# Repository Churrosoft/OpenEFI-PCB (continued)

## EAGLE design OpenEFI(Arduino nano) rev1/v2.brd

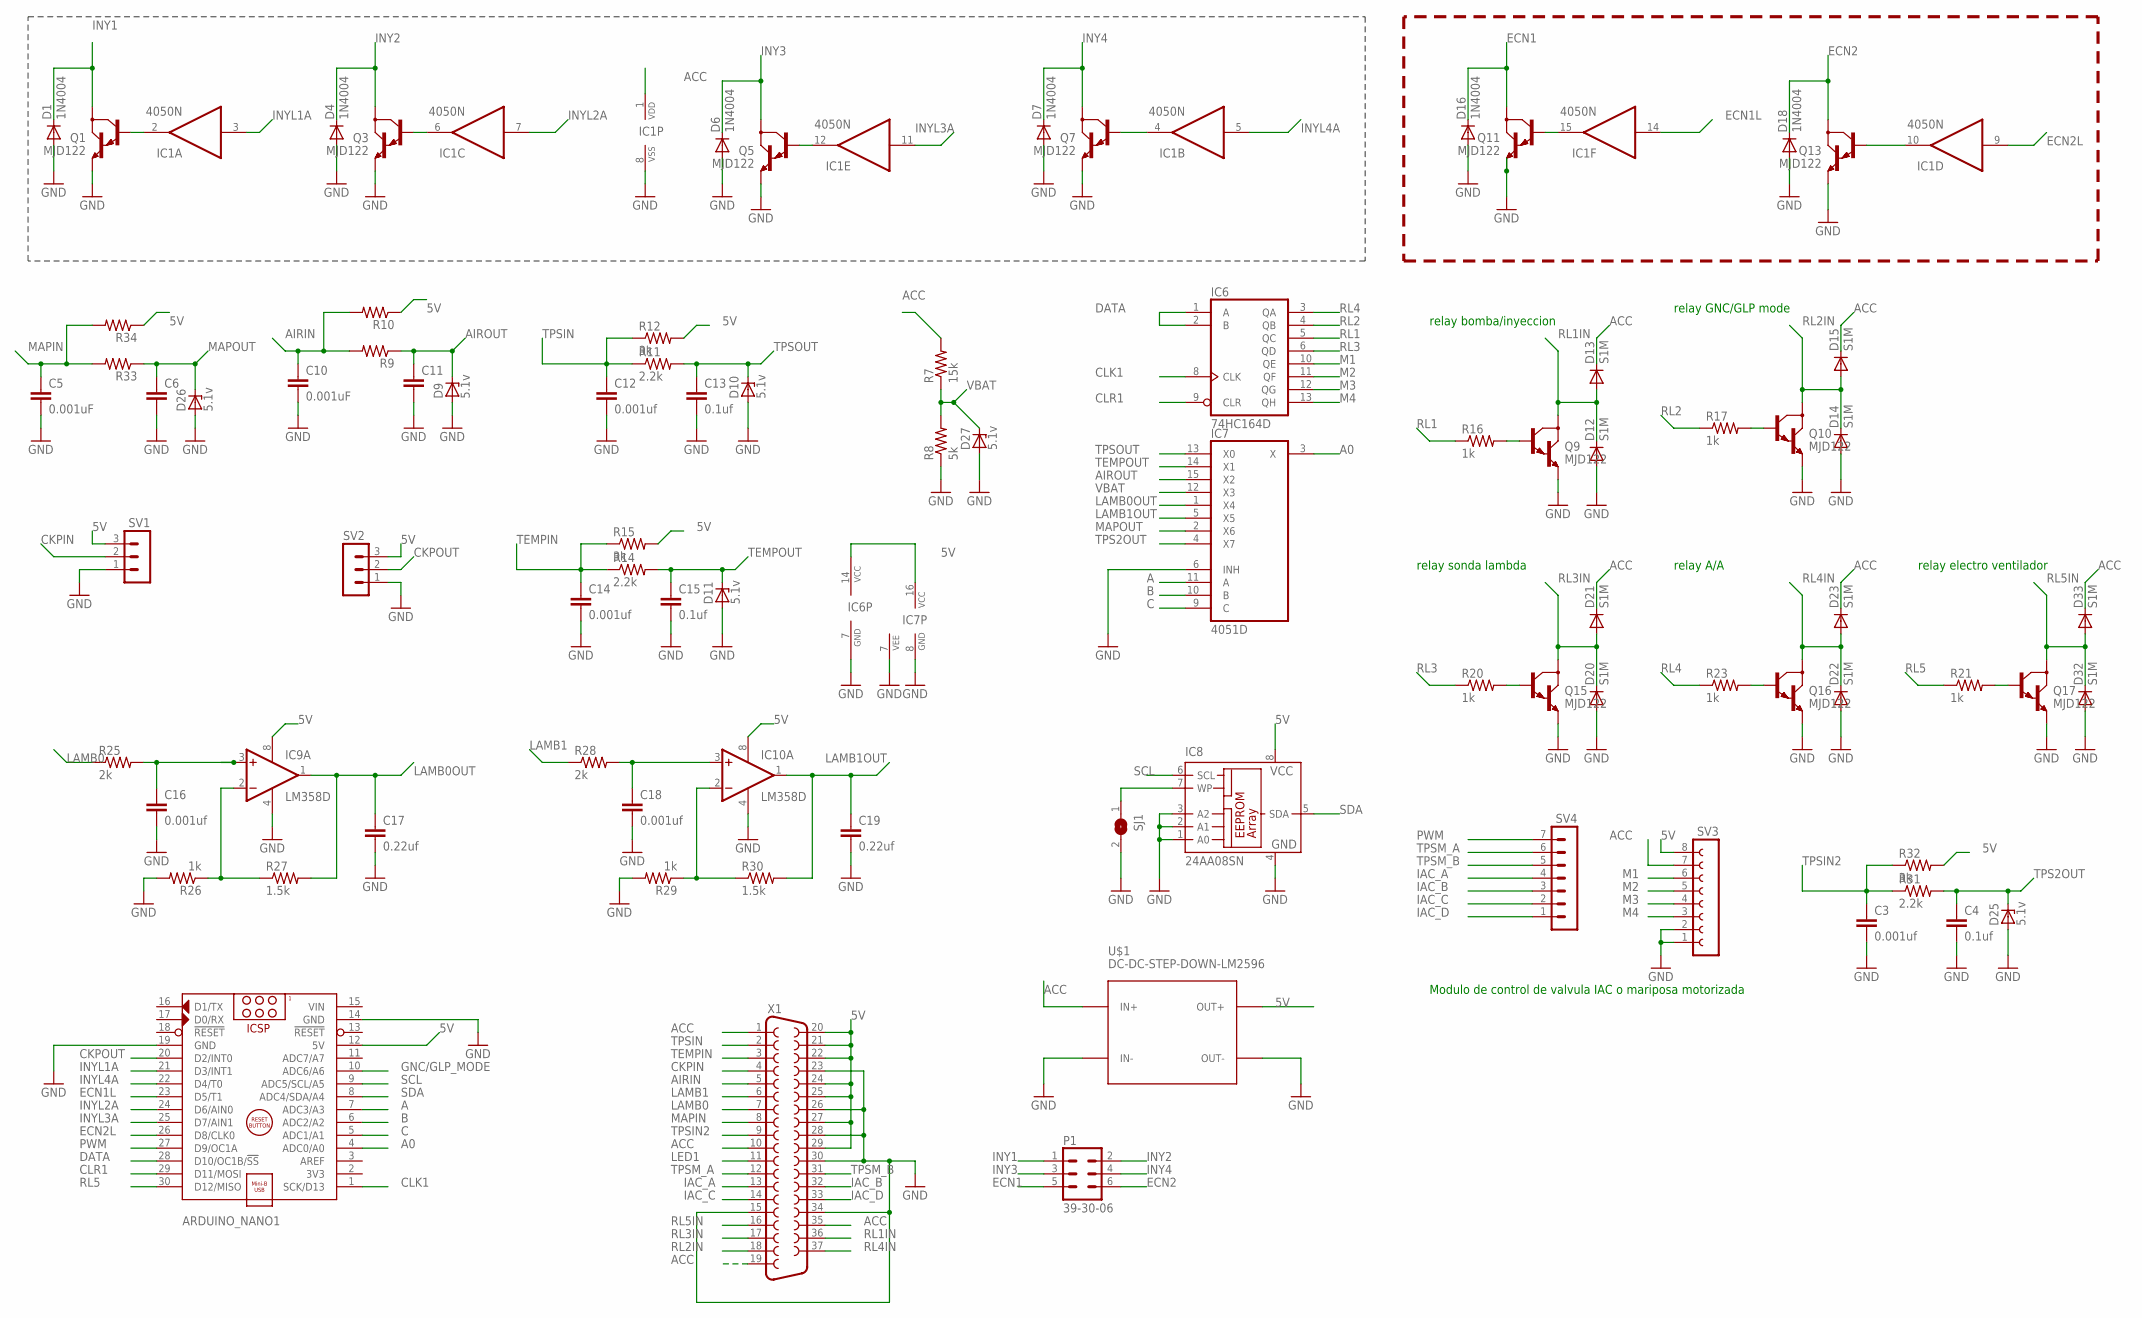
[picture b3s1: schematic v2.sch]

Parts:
ARDUINO_NANO1: ARDUINO_NANO
C3, C12, C14, C16, C18: 0.001uf; C025-025X050
C4, C13, C15: 0.1uf; C025-025X050
C5, C10: 0.001uF; C025-025X050
C6, C11: C-EU025-025X050; C025-025X050
C17, C19: 0.22uf; C025-025X050
D1, D4, D6, D7, D16, D18: 1N4004; DO41-10
D9, D10, D11, D25, D26, D27: 5.1v; ZDIO-5
D12, D13, D14, D15, D20, D21, D22, D23, D32, D33: S1M; SMA
IC1: 4050N; DIL16
IC6: 74HC164D; SO14
IC7: 4051D; SO16
IC8: 24AA08SN; SO-08
IC9, IC10: LM358D; SO08
P1: 39-30-06; 39-30-?06?
Q1, Q3, Q5, Q7, Q9, Q10, Q11, Q13, Q15, Q16, Q17: MJD122; DPAK
R7: 15k; 0204/5
R8: 5k; 0204/5
R9, R10, R33, R34: R-US_0204/5; 0204/5
R11, R14, R31: 2.2k; 0204/5
R12, R15, R32: 3k; 0204/5
R16, R17, R20, R21, R23, R26, R29: 1k; 0204/5
R25, R28: 2k; 0204/5
R27, R30: 1.5k; 0204/5
SJ1: SJW
SV1, SV2: MA03-1
SV3: FE08-1; FE08
SV4: MA07-1
U$1: DC-DC-STEP-DOWN-LM2596
X1: F37HP

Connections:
5V: ARDUINO_NANO1.12 (5V), IC6.14 (VCC), IC7.16 (VCC), IC8.8 (VCC), IC9.8 (V+), IC10.8 (V+), R10.1, R12.2, R15.2, R32.2, R34.1, SV1.3, SV2.3, SV3.8, U$1.OUT+, X1.20, X1.21, X1.22, X1.24, X1.25, X1.27, X1.29
A: ARDUINO_NANO1.7 (ADC3/A3), IC7.11 (A)
A0: ARDUINO_NANO1.4 (ADC0/A0), IC7.3 (X)
ACC: D13.C, D15.C, D21.C, D23.C, D33.C, IC1.1 (VDD), R7.2, SV3.7, U$1.IN+, X1.1, X1.10, X1.19, X1.35
AIRIN: C10.1, R9.2, R10.2, X1.5
AIROUT: C11.1, D9.C, IC7.15 (X2), R9.1
B: ARDUINO_NANO1.6 (ADC2/A2), IC7.10 (B)
C: ARDUINO_NANO1.5 (ADC1/A1), IC7.9 (C)
CKPIN: SV1.2, X1.4
CKPOUT: ARDUINO_NANO1.20 (D2/INT0), SV2.2
CLK1: ARDUINO_NANO1.1 (SCK/D13), IC6.8 (CLK)
CLR1: ARDUINO_NANO1.29 (D11/MOSI), IC6.9 (CLR)
DATA: ARDUINO_NANO1.28 (D10/OC1B/!SS), IC6.1 (A), IC6.2 (B)
ECN1: D16.C, P1.5, Q11.4 (C)
ECN1L: ARDUINO_NANO1.23 (D5/T1), IC1.14 (I)
ECN2: D18.C, P1.6, Q13.4 (C)
ECN2L: ARDUINO_NANO1.26 (D8/CLK0), IC1.9 (I)
GNC/GLP_MODE: ARDUINO_NANO1.10 (ADC6/A6)
GND: ARDUINO_NANO1.14 (GND), ARDUINO_NANO1.19 (GND), C3.2, C4.2, C5.2, C6.2, C10.2, C11.2, C12.2, C13.2, C14.2, C15.2, C16.2, C17.2, C18.2, C19.2, D1.A, D4.A, D6.A, D7.A, D9.A, D10.A, D11.A, D12.A, D14.A, D16.A, D18.A, D20.A, D22.A, D25.A, D26.A, D27.A, D32.A, IC1.8 (VSS), IC6.7 (GND), IC7.6 (INH), IC7.7 (VEE), IC7.8 (GND), IC8.1 (A0), IC8.2 (A1), IC8.3 (A2), IC8.4 (GND), IC9.4 (V-), IC10.4 (V-), Q1.3 (E), Q3.3 (E), Q5.3 (E), Q7.3 (E), Q9.3 (E), Q10.3 (E), Q11.3 (E), Q13.3 (E), Q15.3 (E), Q16.3 (E), Q17.3 (E), R8.1, R26.2, R29.2, SJ1.2, SV1.1, SV2.1, SV3.1, SV3.2, U$1.IN-, U$1.OUT-, X1.15, X1.23, X1.26, X1.28, X1.30, X1.34
IAC_A: SV4.4, X1.13
IAC_B: SV4.3, X1.32
IAC_C: SV4.2, X1.14
IAC_D: SV4.1, X1.33
INY1: D1.C, P1.1, Q1.4 (C)
INY2: D4.C, P1.2, Q3.4 (C)
INY3: D6.C, P1.3, Q5.4 (C)
INY4: D7.C, P1.4, Q7.4 (C)
INYL1A: ARDUINO_NANO1.21 (D3/INT1), IC1.3 (I)
INYL2A: ARDUINO_NANO1.24 (D6/AIN0), IC1.7 (I)
INYL3A: ARDUINO_NANO1.25 (D7/AIN1), IC1.11 (I)
INYL4A: ARDUINO_NANO1.22 (D4/T0), IC1.5 (I)
LAMB0: R25.1, X1.7
LAMB0OUT: C17.1, IC7.1 (X4), IC9.1 (OUT), R27.2
LAMB1: R28.1, X1.6
LAMB1OUT: C19.1, IC7.5 (X5), IC10.1 (OUT), R30.2
LED1: X1.11
M1: IC6.10 (QE), SV3.6
M2: IC6.11 (QF), SV3.5
M3: IC6.12 (QG), SV3.4
M4: IC6.13 (QH), SV3.3
MAPIN: C5.1, R33.2, R34.2, X1.8
MAPOUT: C6.1, D26.C, IC7.2 (X6), R33.1
unnamed: C18.1, IC10.3 (+IN), R28.2
unnamed: IC1.2 (O), Q1.1 (B)
unnamed: IC1.6 (O), Q3.1 (B)
unnamed: Q9.1 (B), R16.2
unnamed: IC1.12 (O), Q5.1 (B)
unnamed: IC1.4 (O), Q7.1 (B)
unnamed: Q17.1 (B), R21.2
unnamed: Q10.1 (B), R17.2
unnamed: IC1.15 (O), Q11.1 (B)
unnamed: IC1.10 (O), Q13.1 (B)
unnamed: Q15.1 (B), R20.2
unnamed: Q16.1 (B), R23.2
unnamed: C16.1, IC9.3 (+IN), R25.2
unnamed: IC9.2 (-IN), R26.1, R27.1
unnamed: IC8.7 (WP), SJ1.1
unnamed: IC10.2 (-IN), R29.1, R30.1
PWM: ARDUINO_NANO1.27 (D9/OC1A), SV4.7
RL1: IC6.5 (QC), R16.1
RL1IN: D12.C, D13.A, Q9.4 (C), X1.36
RL2: IC6.4 (QB), R17.1
RL2IN: D14.C, D15.A, Q10.4 (C), X1.18
RL3: IC6.6 (QD), R20.1
RL3IN: D20.C, D21.A, Q15.4 (C), X1.17
RL4: IC6.3 (QA), R23.1
RL4IN: D22.C, D23.A, Q16.4 (C), X1.37
RL5: ARDUINO_NANO1.30 (D12/MISO), R21.1
RL5IN: D32.C, D33.A, Q17.4 (C), X1.16
SCL: ARDUINO_NANO1.9 (ADC5/SCL/A5), IC8.6 (SCL)
SDA: ARDUINO_NANO1.8 (ADC4/SDA/A4), IC8.5 (SDA)
TEMPIN: C14.1, R14.1, R15.1, X1.3
TEMPOUT: C15.1, D11.C, IC7.14 (X1), R14.2
TPS2OUT: C4.1, D25.C, IC7.4 (X7), R31.2
TPSIN: C12.1, R11.1, R12.1, X1.2
TPSIN2: C3.1, R31.1, R32.1, X1.9
TPSM_A: SV4.6, X1.12
TPSM_B: SV4.5, X1.31
TPSOUT: C13.1, D10.C, IC7.13 (X0), R11.2
VBAT: D27.C, IC7.12 (X3), R7.1, R8.2
VIN: ARDUINO_NANO1.15 (VIN)

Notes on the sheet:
relay bomba/inyeccion
relay GNC/GLP mode
relay sonda lambda
relay A/A
relay electro ventilador
Modulo de control de valvula IAC o mariposa motorizada

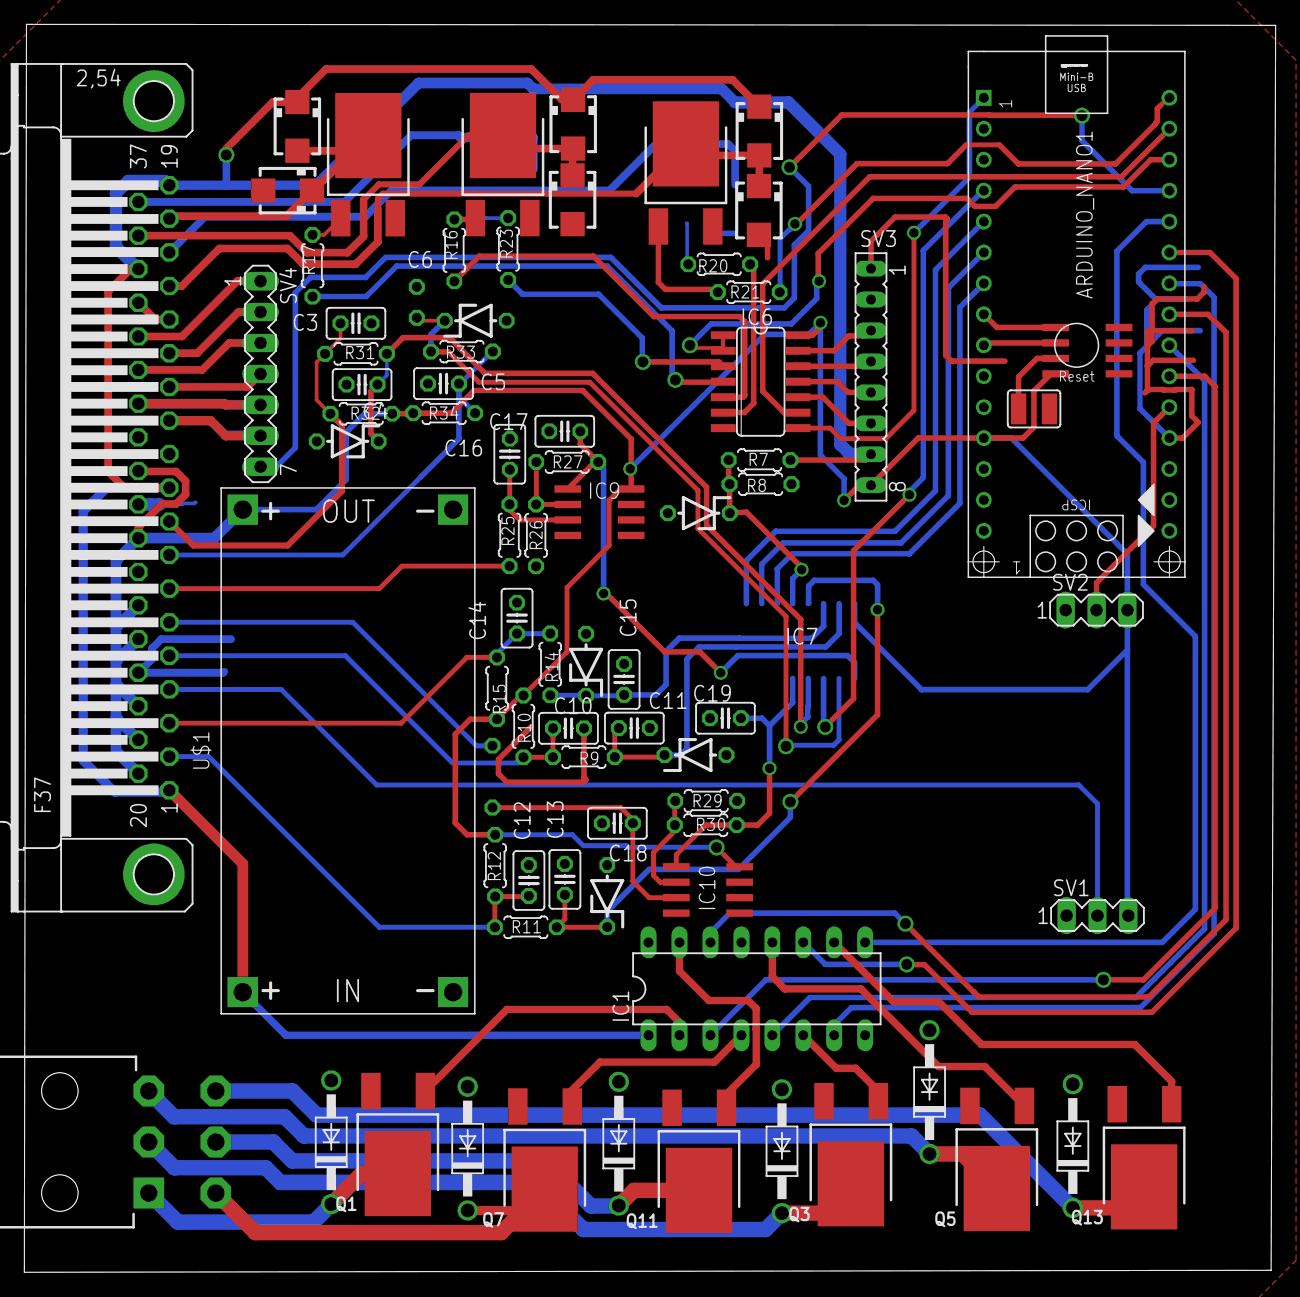
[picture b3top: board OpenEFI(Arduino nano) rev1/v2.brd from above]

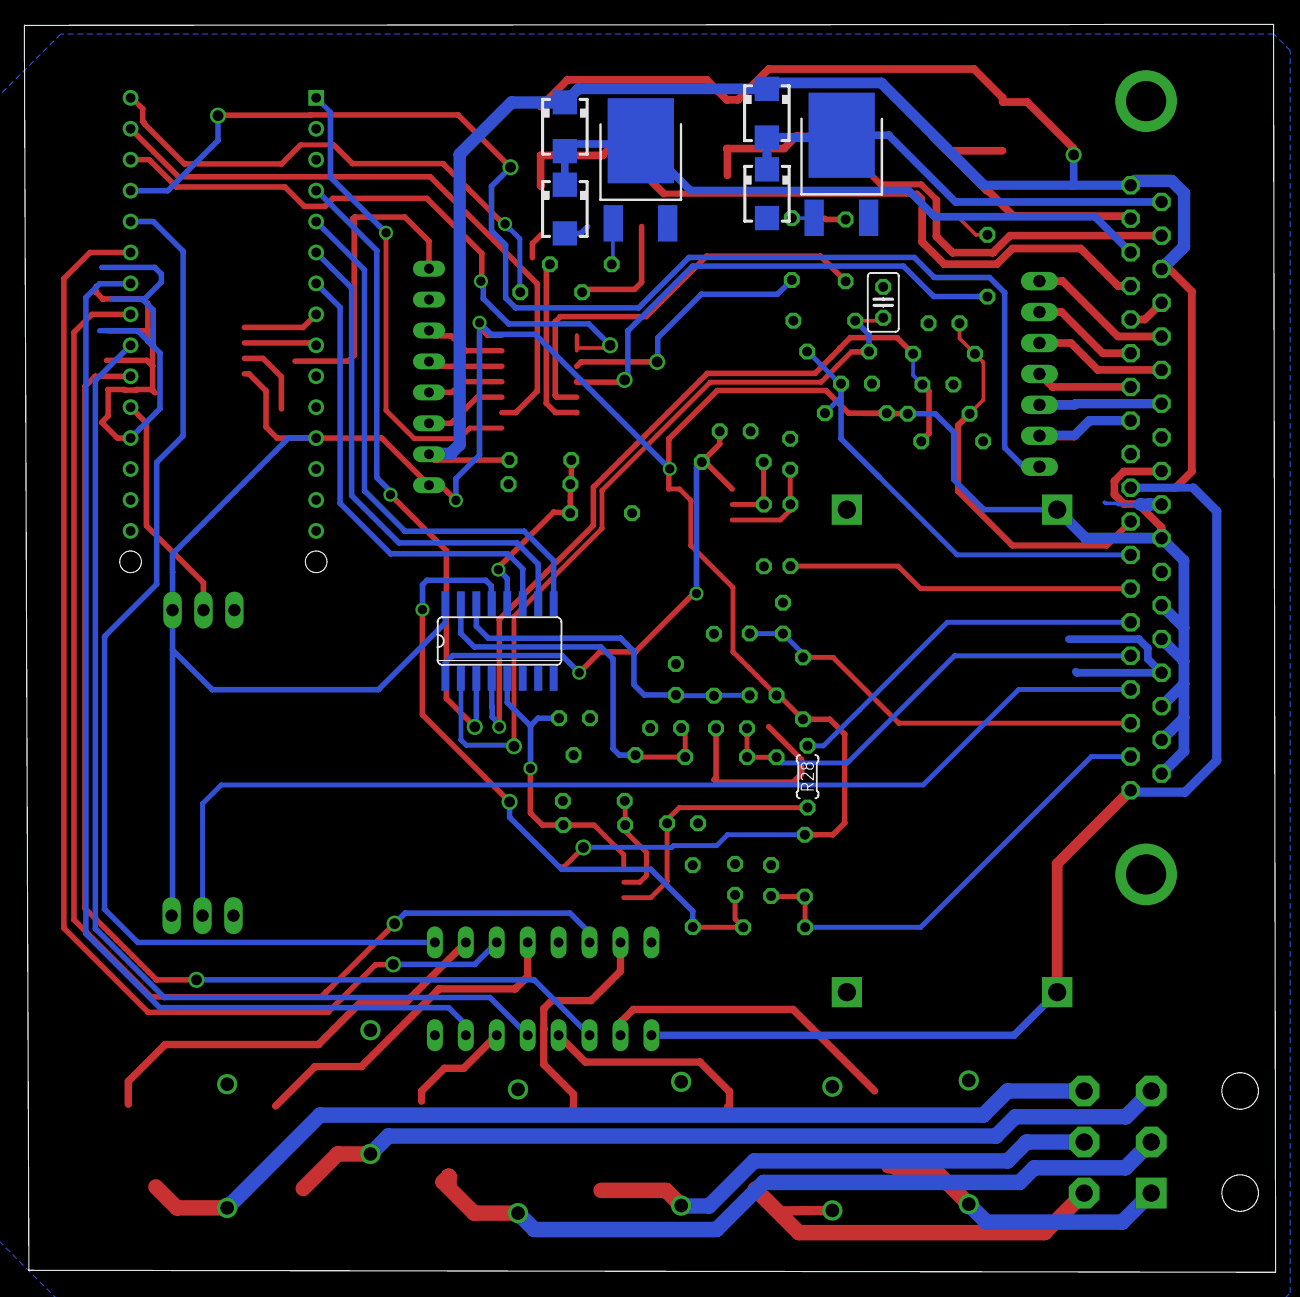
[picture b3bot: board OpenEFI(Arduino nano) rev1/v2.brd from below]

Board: 2 copper layers, 102.7 x 102.5 mm, 85 parts (9 on the bottom side), 78 nets.

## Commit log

2019-04-16 agregado de placas ya existentes
2019-04-19 Variante nueva!!
    Nueva variente de la placa basada en STM32F, se agrego un AtMega328 que va a correr una version modificada de OpenEFI para manejar las salidas e inyectores, ademas se agregaron mas pines de E/S se ca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
2019-04-27 Creacion de V2 del PCB para SMT32F
2019-04-29 cambios menores
2019-04-30 Avances en I/O en rev1
2020-10-03 init v3
2020-10-12 WIP v3 on STM32
2020-11-08 sacando porquerias
2020-11-08 V3 WIP
2020-11-08 el ci ameo'
2020-11-08 los espacios me dan ansiedad
2020-11-08 fix submodules/ pipeline config
2020-11-08 update paths
2020-11-08 fix drc error
2020-11-08 add submodule
2020-11-08 minor fix
2020-11-14 WIP V3
2020-11-26 Update on PMIC
2020-12-08 GPIO
2020-12-27 WIP: PAP Driver
2021-04-01 Last commit to rev3
2021-04-08 uEFI v2.x
2021-04-08 Update git submodules for uEFI
2021-04-10 Making sensor board easier to assemble
2021-04-21 uEFI v2 beta release
2022-01-10 bump to kicad 6, init uEFI v3
2022-02-05 move old boards to __old
2022-02-05 updated github workflows
2022-02-06 fix release type
2022-02-06 bump kibot version
2022-02-06 minor update
2022-02-06 remove InteractiveHtmlBom
2022-02-06 ssh => https submodule
2022-02-06 update v3 pcb libs
2022-02-12 rev3, analog inputs
2022-02-13 rev3 ADC SPI
2022-02-13 rev3, connect PMIC to injector outs
2022-02-18 rev3, PMIC, Relays done
2022-02-18 rev3, jtag
2022-02-18 rev3, complete routing, ERC
2022-02-19 rev3, added acc detect
2022-03-03 fix 10k res
2022-03-24 update kicad_prl
2022-03-24 updated release workflow
2022-03-24 fix release.yml
2022-03-30 added actions, update old files to kicad 6
2022-03-30 branding, fix memory footprint
2022-03-30 added kicad_common
2022-03-30 fix date/version
2022-03-30 revert date autofill
2022-04-13 update jlcpcb kibot
2022-05-01 uEFI rev 3.1.0
2022-05-05 wip v3.1
2022-05-07 Added connector for uEFI
2022-09-24 add ckp sensor setup
2022-09-27 uEFI rev 3.1
2022-09-27 fix? cicd
2022-09-27 change image to v2_k6
2022-09-27 fix dockerhub tag image
2022-09-27 add kibot config files
2022-09-27 test pass config to makefile
2022-09-27 fix config path
2022-09-27 enable verbose logs en kibot
2022-09-28 remove ERC Workflow
2022-09-29 Update LICENSE
2022-09-29 uEFI r3.2
2022-10-12 uEFI rev 3.3
2022-10-25 pre-production files, uEFI v3.4
2022-11-12 fix bom output
2023-01-19 AA wiring, lib&connector update, added eggbug
2023-01-23 Fix SPI pad & connector, add new images, Co-authored-by: Lucacik <name@example.com>
2023-03-04 fix relay tracks
2023-07-01 uEFI v3, fix 12v => 5v overcurrent issue
2023-10-07 rev4 init
2023-10-07 import PCB outline from rusEFI / hellen board
2023-10-09 wip PMIC on rev4 board
2023-10-13 changes on sensors sch
2023-10-14 wip sensors pinout:
2023-10-14 update sensors/connector pinout, added rtc vbatt backup
2023-10-19 WIP Analog frontend
2023-10-19 WIP analog frontend, init ckp"
2023-10-20 WIP relay driver
2023-10-22 WIP CKP/CMP
2023-10-22 fix board errors
2023-10-22 add tacho driver
2023-10-23 wip SD card
2023-10-28 wip relay pcb
2023-11-01 WIP SPI
2023-11-02 fix pcb size/wideband
2023-11-11 WIP Rev4 SPI
2023-11-11 Rev4: add all MCU signals
2023-11-11 Rev4 fix DRC errors
2023-11-12 Rev4 WIP LCSC assigments
2023-12-05 update footprints
2024-04-07 update 32khz crystal
